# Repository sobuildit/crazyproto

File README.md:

# crazyproto
Crazy ideas for electronics prototyping. Sometimes we just have fun with it.

Projects:

**Hex-SOT23** Can we use hexagonal circuit traces to define a fixed layout to route a non-trivial circuit to a SOT23 footprint (e.g. NPN Bipolar transistor) such that the component placement alone defines the circuit?

The concept is simple enough, the nodes (or wires/pads) in the centre {1,2,3} are the device pins, as identified on the PCB. The connection nodes are {A,B,C} and the 'power' nodes are {Vcc,Gnd} but those are just names, you can use them for anything.

The hex tiles with a single label present the same signal on both sides of the PCB.
The hex tiles with two labels present the top signal on the top surface and the bottom signal on the bottom. No surprises.

Finally, nodes of the form (letter)(number) e.g. A2 are uncommitted nodes, that are useful for intermediate signals, and have no association with a connector pin or device pin.

The schematic is rough. Really rough (this is only a toy!) Also, the PCB design is also only a quick lashup and is drawn by hand, for fun. Gerbers are provided as-is, have not yet been manufactured, but I may do so in the future.

Do not use for RF! Parasitics will be off-the-chart bad!

Cost from allpcb, for quantity 10, HASL finish is estimated at about $24 USD before import duty, for the UK. Your country may differ. Have fun!

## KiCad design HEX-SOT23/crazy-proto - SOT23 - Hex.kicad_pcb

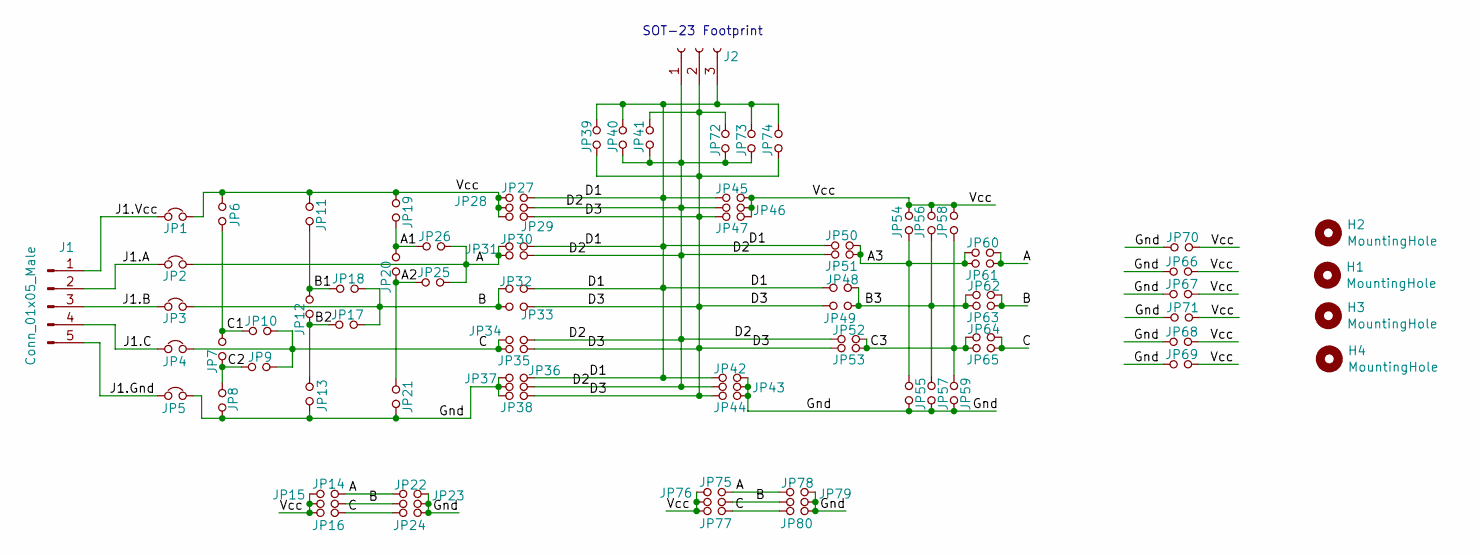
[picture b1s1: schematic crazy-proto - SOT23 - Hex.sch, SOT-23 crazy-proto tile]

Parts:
H1, H2, H3, H4: MountingHole; MountingHole_3.2mm_M3
J1: Conn_01x05_Male; Pin_Header_Straight_1x05_Pitch2.54mm
J2: Conn_01x03_Female; SOT-23
JP1, JP2, JP3, JP4, JP5: Jumper_NC_Small; NC_0603_HandSoldering
JP6, JP7, JP8, JP9, JP10, JP11, JP12, JP13, JP14, JP15, JP16, JP17, JP18, JP19, JP20, JP21, JP22, JP23, JP24, JP25, JP26, JP27, JP28, JP29, JP30, JP31, JP32, JP33, JP34, JP35, JP36, JP37, JP38, JP39, JP40, JP41, JP42, JP43, JP44, JP45, JP46, JP47, JP48, JP49, JP50, JP51, JP52, JP53, JP54, JP55, JP56, JP57, JP58, JP59, JP60, JP61, JP62, JP63, JP64, JP65, JP66, JP67, JP68, JP69, JP70, JP71, JP72, JP73, JP74, JP75, JP76, JP77, JP78, JP79, JP80: Jumper_NO_Small; R_0603_HandSoldering

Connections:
/A: JP2.2, JP14.1, JP22.1, JP25.1, JP26.1, JP30.2, JP31.2, JP60.1, JP61.1, JP75.1, JP78.1
/A1: JP19.1, JP20.2, JP26.2
/A2: JP20.1, JP21.2, JP25.2
/A3: JP50.1, JP51.1, JP54.1, JP55.1, JP60.2, JP61.2
/B: JP3.2, JP15.1, JP17.1, JP18.1, JP23.1, JP32.2, JP33.2, JP62.1, JP63.1, JP76.1, JP79.1
/B1: JP11.1, JP12.2, JP18.2
/B2: JP12.1, JP13.2, JP17.2
/B3: JP48.1, JP49.1, JP56.1, JP57.1, JP62.2, JP63.2
/C: JP4.2, JP9.1, JP10.1, JP16.1, JP24.1, JP34.2, JP35.2, JP64.1, JP65.1, JP77.1, JP80.1
/C1: JP6.1, JP7.2, JP10.2
/C2: JP7.1, JP8.2, JP9.2
/C3: JP52.1, JP53.1, JP58.1, JP59.1, JP64.2, JP65.2
/D1: J2.3, JP27.1, JP30.1, JP32.1, JP36.1, JP39.1, JP40.1, JP42.1, JP45.1, JP48.2, JP50.2, JP73.1, JP74.1; also elsewhere on the board
/D2: J2.1, JP28.1, JP31.1, JP34.1, JP37.1, JP40.2, JP41.2, JP43.1, JP46.1, JP51.2, JP52.2, JP72.2, JP73.2; also elsewhere on the board
/D3: J2.2, JP29.1, JP33.1, JP35.1, JP38.1, JP39.2, JP41.1, JP44.1, JP47.1, JP49.2, JP53.2, JP72.1, JP74.2; also elsewhere on the board
/Gnd: JP5.2, JP8.1, JP13.1, JP21.1, JP22.2, JP23.2, JP24.2, JP36.2, JP37.2, JP38.2, JP42.2, JP43.2, JP44.2, JP55.2, JP57.2, JP59.2, JP66.2, JP67.2, JP68.2, JP69.2, JP70.2, JP71.2, JP78.2, JP79.2, JP80.2
/J1.A: J1.2, JP2.1
/J1.B: J1.3, JP3.1
/J1.C: J1.4, JP4.1
/J1.Gnd: J1.5, JP5.1
/J1.Vcc: J1.1, JP1.1
/Vcc: JP1.2, JP6.2, JP11.2, JP14.2, JP15.2, JP16.2, JP19.2, JP27.2, JP28.2, JP29.2, JP45.2, JP46.2, JP47.2, JP54.2, JP56.2, JP58.2, JP66.1, JP67.1, JP68.1, JP69.1, JP70.1, JP71.1, JP75.2, JP76.2, JP77.2

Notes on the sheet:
SOT-23 Footprint

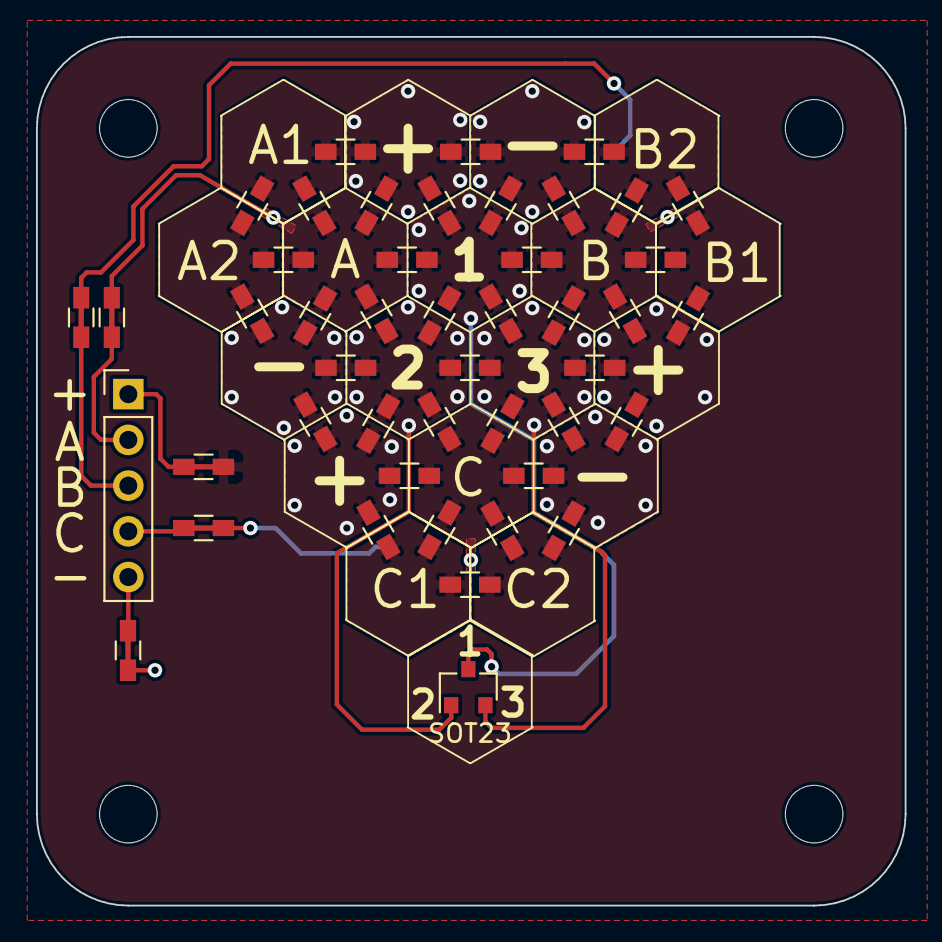
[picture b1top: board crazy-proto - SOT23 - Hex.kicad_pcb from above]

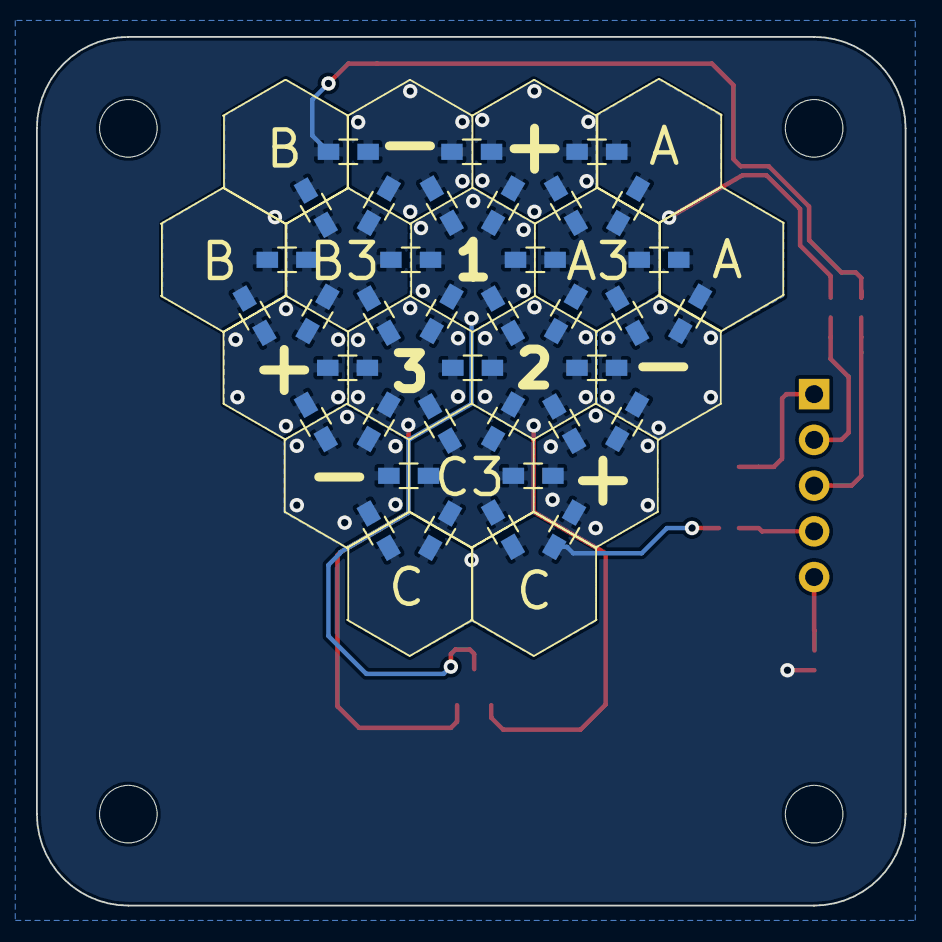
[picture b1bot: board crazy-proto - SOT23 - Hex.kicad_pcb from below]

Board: 2 copper layers, 48.3 x 48.3 mm, 86 parts (36 on the bottom side), 22 nets.

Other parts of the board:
SOT23: Conn_01x03_Female; SOT-23

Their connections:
/D1: SOT23.3; also elsewhere on the board
/D2: SOT23.1; also elsewhere on the board
/D3: SOT23.2; also elsewhere on the board

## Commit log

2019-03-13 Initial commit of local copy
